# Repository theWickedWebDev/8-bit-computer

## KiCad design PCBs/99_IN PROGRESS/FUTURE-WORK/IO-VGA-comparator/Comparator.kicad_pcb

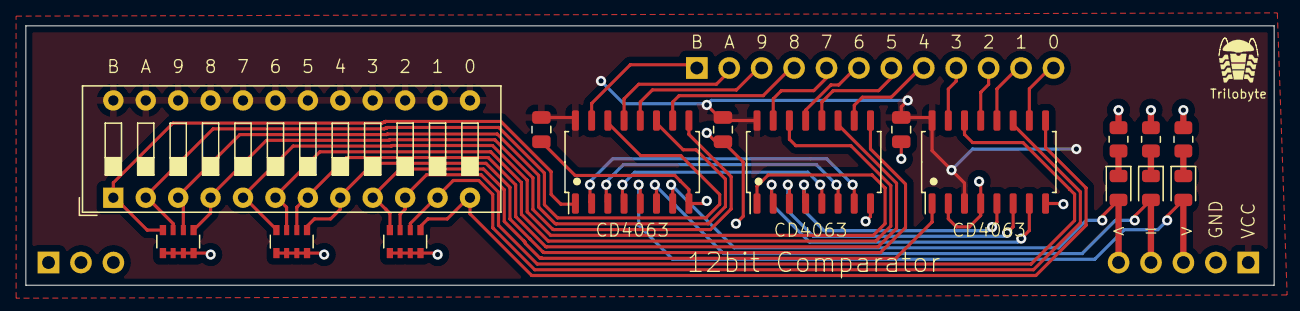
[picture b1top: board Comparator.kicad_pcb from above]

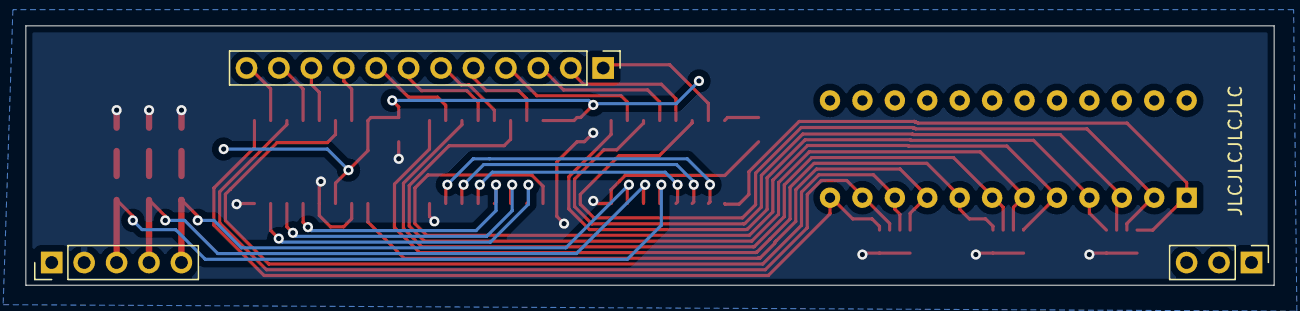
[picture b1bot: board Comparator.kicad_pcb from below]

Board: 2 copper layers, 97.8 x 20.3 mm, 19 parts (3 on the bottom side), 38 nets.

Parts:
C11, C12, C13: C; C_0805_2012Metric
D4, D5, D6: LED; LED_0805_2012Metric
J7: Conn_01x12; PinHeader_1x12_P2.54mm_Vertical
J8: Conn_01x05; PinHeader_1x05_P2.54mm_Vertical
J29: Conn_01x03; PinHeader_1x03_P2.54mm_Vertical
R4, R5, R6: R_US; R_0805_2012Metric
RN4, RN5, RN6: R_Pack04; R_Array_Convex_4x0603
SW2: SW_DIP_x12; SW_DIP_SPSTx12_Slide_9.78x32.66mm_W7.62mm_P2.54mm
U4, U5, U6: CD4063; SOIC-16_4.55x10.3mm_P1.27mm

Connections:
/Horizontal Timing/Comparator/D0_0: RN4.1 (R1.1), SW2.12, U4.9 (B0)
/Horizontal Timing/Comparator/D0_1: RN4.2 (R2.1), SW2.11, U4.11 (B1)
/Horizontal Timing/Comparator/D0_2: RN4.3 (R3.1), SW2.10, U4.14 (B2)
/Horizontal Timing/Comparator/D0_3: RN4.4 (R4.1), SW2.9, U4.1 (B3)
/Horizontal Timing/Comparator/D0_4: RN5.1 (R1.1), SW2.8, U5.9 (B0)
/Horizontal Timing/Comparator/D0_5: RN5.2 (R2.1), SW2.7, U5.11 (B1)
/Horizontal Timing/Comparator/D0_6: RN5.3 (R3.1), SW2.6, U5.14 (B2)
/Horizontal Timing/Comparator/D0_7: RN5.4 (R4.1), SW2.5, U5.1 (B3)
/Horizontal Timing/Comparator/D0_8: RN6.1 (R1.1), SW2.4, U6.9 (B0)
/Horizontal Timing/Comparator/D0_9: RN6.2 (R2.1), SW2.3, U6.11 (B1)
/Horizontal Timing/Comparator/D0_10: RN6.3 (R3.1), SW2.2, U6.14 (B2)
/Horizontal Timing/Comparator/D0_11: RN6.4 (R4.1), SW2.1, U6.1 (B3)
COUNT0: J7.12, U4.10 (A0)
COUNT1: J7.11, U4.12 (A1)
COUNT2: J7.10, U4.13 (A2)
COUNT3: J7.9, U4.15 (A3)
COUNT4: J7.8, U5.10 (A0)
COUNT5: J7.7, U5.12 (A1)
COUNT6: J7.6, U5.13 (A2)
COUNT7: J7.5, U5.15 (A3)
COUNT8: J7.4, U6.10 (A0)
COUNT9: J7.3, U6.12 (A1)
COUNT10: J7.2, U6.13 (A2)
COUNT11: J7.1, U6.15 (A3)
GND: C11.2, C12.2, C13.2, J8.2, R4.2, R5.2, R6.2, RN4.5 (R4.2), RN4.6 (R3.2), RN4.7 (R2.2), RN4.8 (R1.2), RN5.5 (R4.2), RN5.6 (R3.2), RN5.7 (R2.2), RN5.8 (R1.2), RN6.5 (R4.2), RN6.6 (R3.2), RN6.7 (R2.2), RN6.8 (R1.2), U4.2 (Ia<b), U4.4 (Ia>b), U4.8 (GND), U5.8 (GND), U6.8 (GND)
unnamed: D4.1 (K), R4.1
unnamed: D5.1 (K), R5.1
unnamed: D6.1 (K), R6.1
unnamed: U4.5 (Oa>b), U5.4 (Ia>b)
unnamed: U4.6 (Oa=b), U5.3 (Ia=b)
unnamed: U4.7 (Oa<b), U5.2 (Ia<b)
unnamed: U5.5 (Oa>b), U6.4 (Ia>b)
unnamed: U5.6 (Oa=b), U6.3 (Ia=b)
unnamed: U5.7 (Oa<b), U6.2 (Ia<b)
VCC: C11.1, C12.1, C13.1, J8.1, SW2.13, SW2.14, SW2.15, SW2.16, SW2.17, SW2.18, SW2.19, SW2.20, SW2.21, SW2.22, SW2.23, SW2.24, U4.3 (Ia=b), U4.16 (VCC), U5.16 (VCC), U6.16 (VCC)
~EQ0: D5.2 (A), J8.4, U6.6 (Oa=b)
~GT0: D6.2 (A), J8.3, U6.5 (Oa>b)
~LT0: D4.2 (A), J8.5, U6.7 (Oa<b)

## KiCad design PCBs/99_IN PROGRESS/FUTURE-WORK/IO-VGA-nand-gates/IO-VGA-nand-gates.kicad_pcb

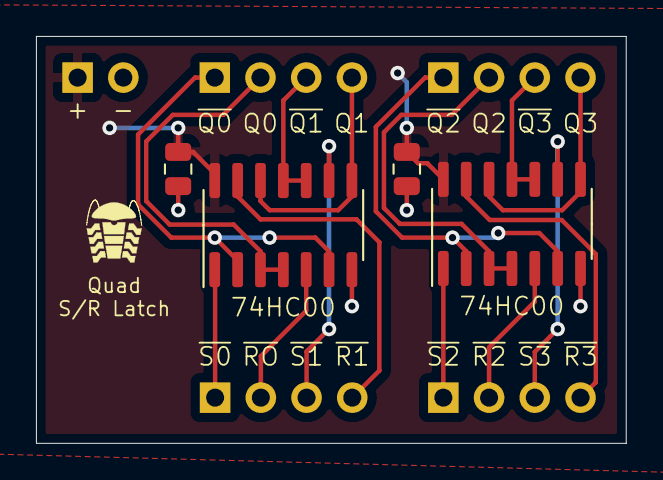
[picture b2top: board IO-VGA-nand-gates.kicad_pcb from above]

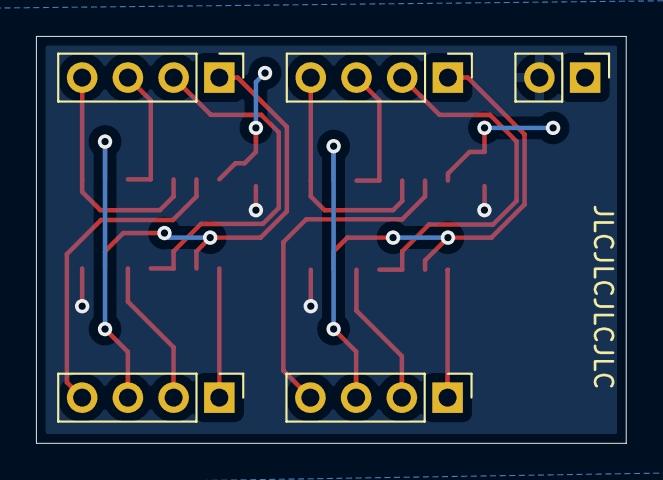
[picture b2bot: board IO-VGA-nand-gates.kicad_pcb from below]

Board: 2 copper layers, 32.8 x 22.6 mm, 9 parts (5 on the bottom side), 18 nets.

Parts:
C1, C2: C; C_0805_2012Metric
J1, J3, J4, J5: Conn_01x04; PinHeader_1x04_P2.54mm_Vertical
J2: Conn_01x02; PinHeader_1x02_P2.54mm_Vertical
U1, U2: 74LS00; SOIC-14_3.9x8.7mm_P1.27mm

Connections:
/Q0: J5.2, U1.3, U1.4
/Q1: J5.4, U1.8, U1.12
/Q2: J4.2, U2.3, U2.4
/Q3: J4.4, U2.8, U2.12
/~Q0: J5.1, U1.2, U1.6
/~Q1: J5.3, U1.10, U1.11
/~Q2: J4.1, U2.2, U2.6
/~Q3: J4.3, U2.10, U2.11
/~R0: J1.2, U1.5
/~R1: J1.4, U1.13
/~R2: J3.2, U2.5
/~R3: J3.4, U2.13
/~S0: J1.1, U1.1
/~S1: J1.3, U1.9
/~S2: J3.1, U2.1
/~S3: J3.3, U2.9
GND: C1.2, C2.2, J2.2, U1.7 (GND), U2.7 (GND)
VCC: C1.1, C2.1, J2.1, U1.14 (VCC), U2.14 (VCC)

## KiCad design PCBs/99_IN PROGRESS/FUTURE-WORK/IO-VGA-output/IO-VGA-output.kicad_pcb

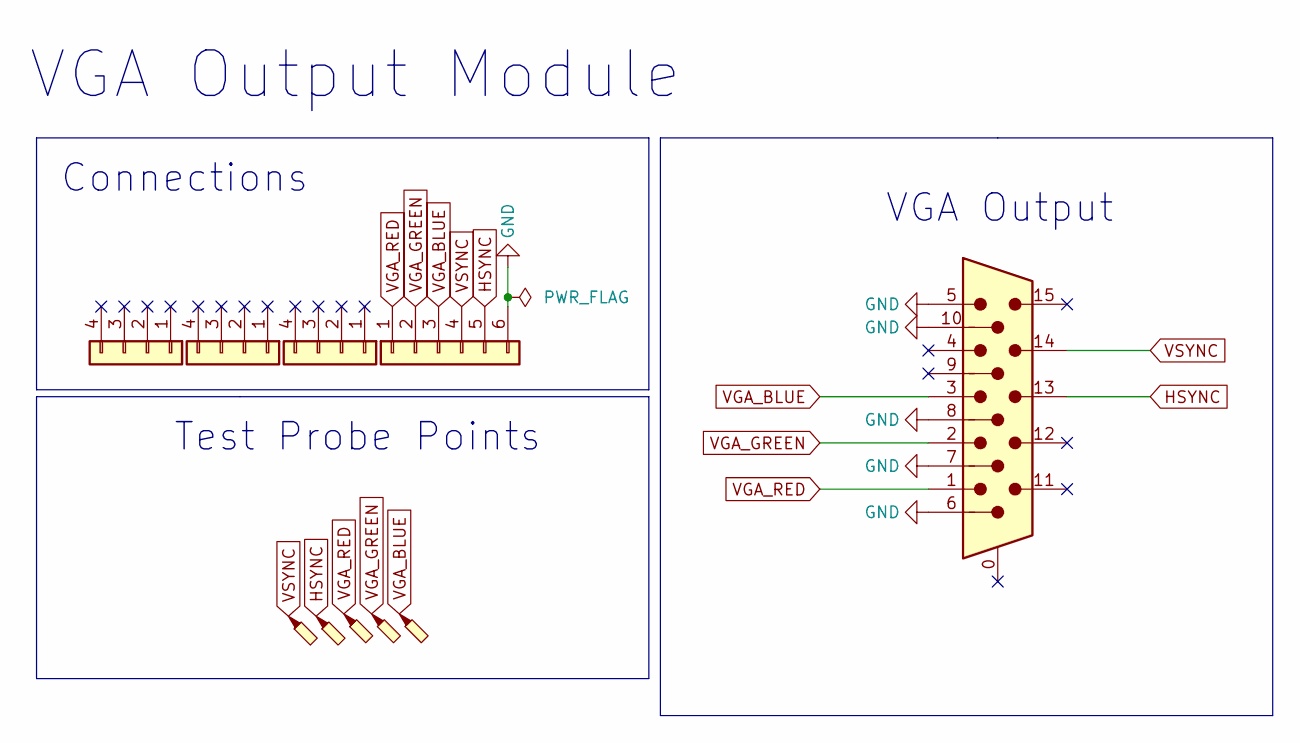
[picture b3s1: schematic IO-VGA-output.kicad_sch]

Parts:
J1: DB15_Male_HighDensity_MountingHoles; DSUB-15-HD_Female_Horizontal_P2.29x1.98mm_EdgePinOffset8.35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
J2, J4, J5: Conn_01x04; PinHeader_1x04_P2.54mm_Vertical
J3: Conn_01x06; PinHeader_1x06_P2.54mm_Vertical
TP1, TP2, TP3, TP4, TP5: TestPoint_Probe; TestPoint_Pad_D3.0mm

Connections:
GND: J1.5, J1.6, J1.7, J1.8, J1.10, J3.6
HSYNC: J1.13, J3.5, TP4.1
VGA_BLUE: J1.3, J3.3, TP1.1
VGA_GREEN: J1.2, J3.2, TP2.1
VGA_RED: J1.1, J3.1, TP3.1
VSYNC: J1.14, J3.4, TP5.1

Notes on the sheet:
VGA Output
Test Probe Points
Connections
VGA Output Module

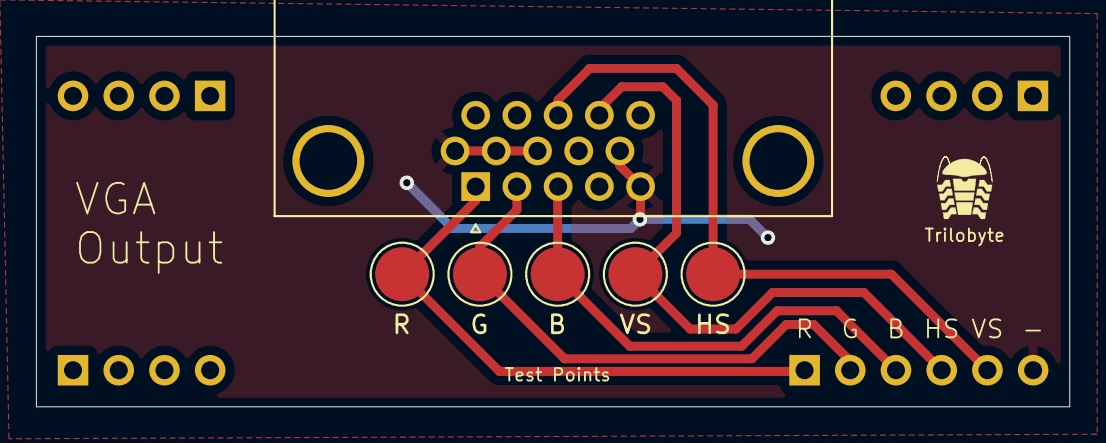
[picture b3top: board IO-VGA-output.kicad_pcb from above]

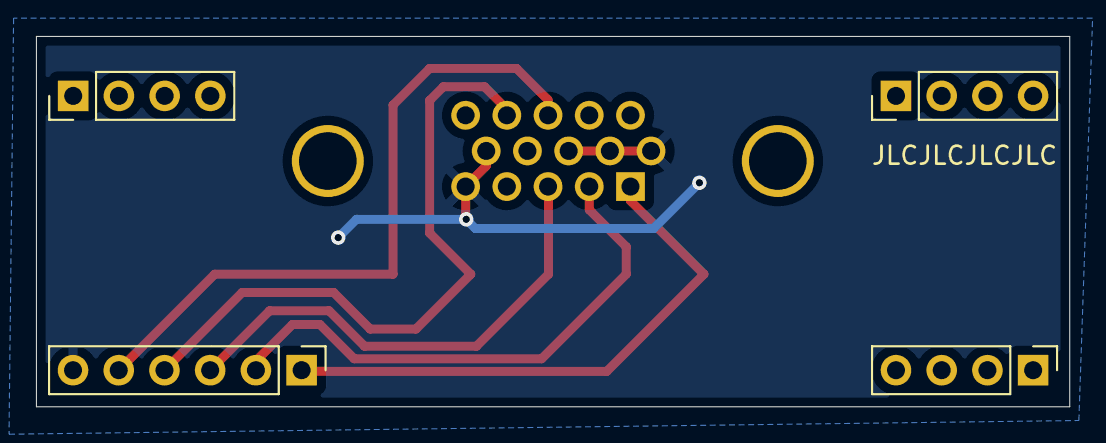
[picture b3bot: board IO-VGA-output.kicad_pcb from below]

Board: 2 copper layers, 57.4 x 20.6 mm, 10 parts (4 on the bottom side), 6 nets.

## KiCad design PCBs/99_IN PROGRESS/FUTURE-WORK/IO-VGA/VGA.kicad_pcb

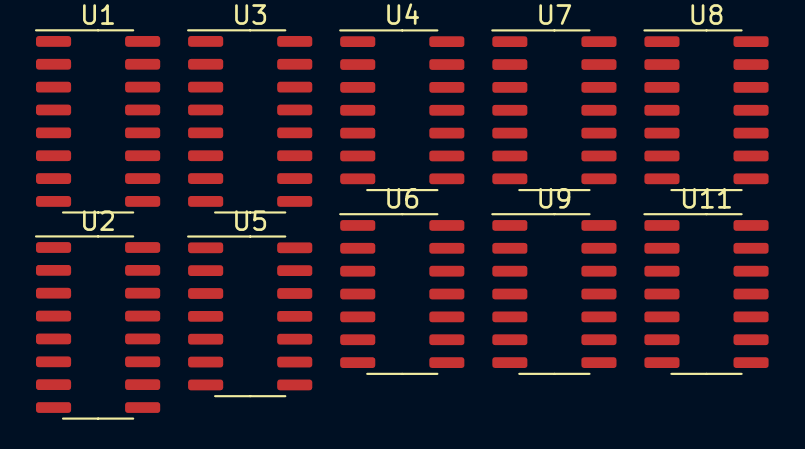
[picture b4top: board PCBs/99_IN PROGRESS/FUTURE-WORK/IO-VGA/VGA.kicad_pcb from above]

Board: 2 copper layers, 10 parts (0 on the bottom side), 2 nets, no tracks yet.

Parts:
U1, U2, U3: SN74HC161DR; SOIC-16_3.9x9.9mm_P1.27mm
U4, U5: 74HC04; SOIC-14_3.9x8.7mm_P1.27mm
U6, U7, U9, U11: CD74HC30M96; SOIC-14_3.9x8.7mm_P1.27mm
U8: SN74HC00DR; SOIC-14_3.9x8.7mm_P1.27mm

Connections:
GND: U1.8, U2.8, U3.8, U4.7, U5.7, U6.7, U7.7, U8.7, U9.7, U11.7
VCC: U1.9, U1.16, U2.9, U2.16, U3.9, U3.16, U4.14, U5.14, U6.14, U7.14, U8.14, U9.14, U11.14

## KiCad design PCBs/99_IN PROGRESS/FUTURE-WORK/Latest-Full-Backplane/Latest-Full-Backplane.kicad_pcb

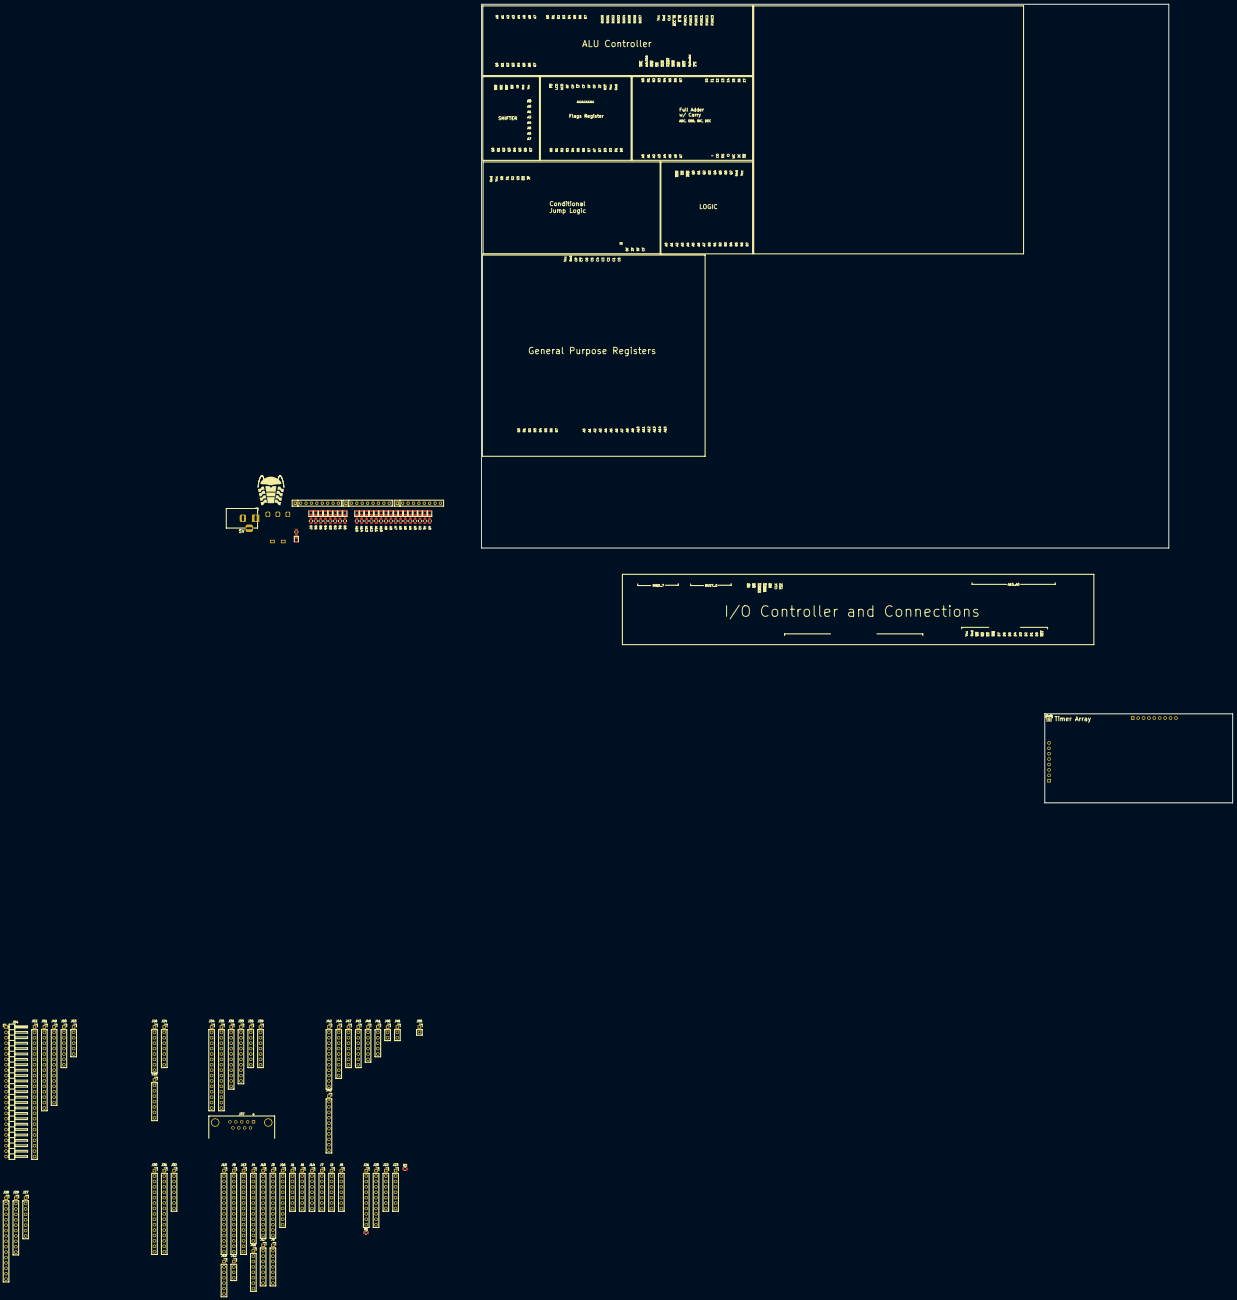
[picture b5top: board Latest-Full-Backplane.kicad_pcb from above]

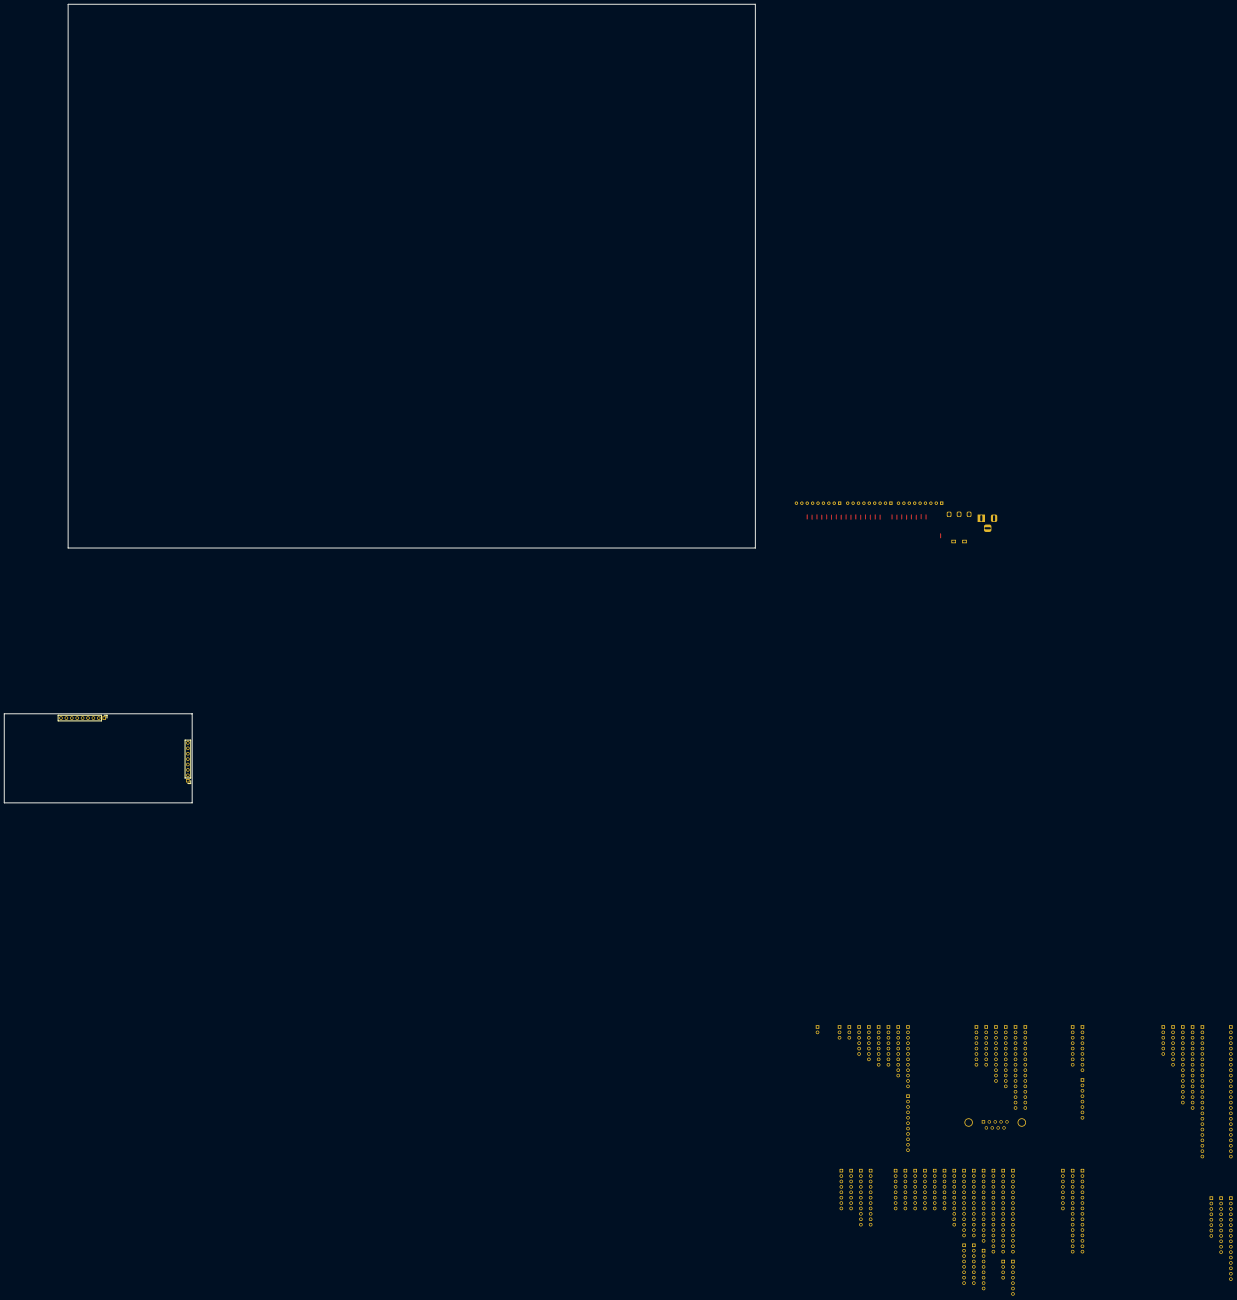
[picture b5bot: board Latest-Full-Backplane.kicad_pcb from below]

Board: 2 copper layers, 113 parts (2 on the bottom side), 160 nets.

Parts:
D1, D2, D3, D4, D5, D6, D7, D8, D9, D10, D11, D12, D13, D14, D15, D16, D17, D18, D19, D20, D21, D22, D23, D24, D25: LED; LED_0805_2012Metric
J1, J2, J5, J6, J7, J8, J11, J14, J17, J22, J23, J24, J25, J27, J32, J36, J39, J43, J47, J50: Conn_01x08; PinSocket_1x08_P2.54mm_Vertical
J1#2: Conn_01x08; PinHeader_1x08_P2.54mm_Vertical
J2#2: Conn_01x09; PinHeader_1x09_P2.54mm_Vertical
J3, J10: Conn_01x13; PinSocket_1x13_P2.54mm_Vertical
J4: Conn_01x14; PinSocket_1x14_P2.54mm_Vertical
J9, J13, J15, J28, J30, J31, J34, J35, J51: Conn_01x16; PinSocket_1x16_P2.54mm_Vertical
J12: Conn_01x04; PinSocket_1x04_P2.54mm_Vertical
J16, J21, J29, J33, J40: Conn_01x11; PinSocket_1x11_P2.54mm_Vertical
J18: Barrel_Jack_MountingPin; BarrelJack_Horizontal
J19, J48: Conn_01x07; PinSocket_1x07_P2.54mm_Vertical
J20: Conn_01x12; PinSocket_1x11_P2.54mm_Vertical
J26: Conn_01x09; PinSocket_1x09_P2.54mm_Vertical
J37: Conn_01x09; DSUB-9_Female_Horizontal_P2.77x2.84mm_EdgePinOffset4.94mm_H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
J38, J42: Conn_01x12; PinSocket_1x12_P2.54mm_Vertical
J41, J53: Conn_01x06; PinSocket_1x06_P2.54mm_Vertical
J44: Conn_01x10; PinSocket_1x10_P2.54mm_Vertical
J45, J46: Conn_01x03; PinSocket_1x03_P2.54mm_Vertical
J49: Conn_01x15; PinSocket_1x15_P2.54mm_Vertical
J52: Conn_01x25; PinSocket_1x25_P2.54mm_Vertical
J54: Conn_01x25; PinHeader_1x25_P2.54mm_Horizontal
J55: Conn_01x02; PinSocket_1x02_P2.54mm_Vertical
R1, R2, R3, R4, R5, R6, R7, R8, R9, R10, R11, R12, R13, R14, R15, R16, R17, R18, R19, R20, R21, R22, R23, R24, R25, R26, R27: R_US; R_0805_2012Metric
RN2, RN3: R_Network08; R_Array_SIP9
RN': R_Network08; R_Array_SIP9
SW1: SW_DPDT_x2; 100SP1T1B4M6RE

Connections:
/ADDR0: J20.1, J23.1, J29.1, J43.1
/ADDR1: J20.2, J23.2, J29.2, J43.2
/ADDR2: J20.3, J23.3, J29.3, J43.3
/ADDR3: J20.4, J23.4, J29.4, J43.4
/ADDR4: J20.5, J23.5, J29.5, J30.4, J43.5
/ADDR5: J20.6, J23.6, J29.6, J43.6
/ADDR6: J20.7, J23.7, J29.7, J43.7
/ADDR7: J20.8, J23.8, J26.9, J29.8, J43.8
/ADDR8: J20.9, J26.8, J29.9
/ADDR9: J20.10, J26.7, J29.10
/ADDR10: J20.11, J26.6, J29.11
/ALU/ALU_A0: J17.1, J18.1, J19.1
/ALU/ALU_A1: J17.2, J18.2, J19.2
/ALU/ALU_A2: J17.3, J18.3, J19.3
/ALU/ALU_A3: J17.4, J19.4
/ALU/ALU_A4: J17.5, J19.5
/ALU/ALU_A5: J16.11, J17.6, J19.6
/ALU/ALU_A6: J16.10, J17.7, J19.7
/ALU/ALU_A7: J6.6, J16.9, J17.8
/ALU/ALU_B0: J14.1, J15.1, J16.8
/ALU/ALU_B1: J14.2, J15.2, J16.7
/ALU/ALU_B2: J14.3, J15.3, J16.6
/ALU/ALU_B3: J14.4, J15.4, J16.5
/ALU/ALU_B4: J14.5, J15.5, J16.4
/ALU/ALU_B5: J14.6, J15.6, J16.3
/ALU/ALU_B6: J14.7, J15.7, J16.2
/ALU/ALU_B7: J6.5, J14.8, J15.8, J16.1
/ALU/ALU_FUNC_0: J2.4, J36.6
/ALU/ALU_FUNC_1: J2.3, J36.7
/ALU/ALU_FUNC_2: J2.2, J36.8
/ALU/ALU_Q0: J10.4, J11.8, J13.8
/ALU/ALU_Q1: J10.5, J11.7, J13.7
/ALU/ALU_Q2: J10.6, J11.6, J13.6
/ALU/ALU_Q3: J10.7, J11.5, J13.5
/ALU/ALU_Q4: J10.8, J11.4, J12.4, J13.4
/ALU/ALU_Q5: J10.9, J11.3, J12.3, J13.3
/ALU/ALU_Q6: J6.8, J10.10, J11.2, J12.2, J13.2
/ALU/ALU_Q7: J6.7, J10.11, J11.1, J12.1, J13.1
/ALU/CF: J1.7, J4.4, J7.4
/ALU/CLOCK: J21.9, J24.4, J30.6, J34.2, J40.5
/ALU/JCC_ADR0: J3.6, J37.1
/ALU/JCC_ADR1: J3.5, J37.3
/ALU/JCC_ADR2: J3.4, J37.2
/ALU/JCC_ADR3: J3.3, J37.4
/ALU/OF: J1.5, J4.1
/ALU/SF: J1.6, J4.3
/ALU/ZF: J1.4, J4.2
/ALU/~JCC_EN: J3.2, J37.5
/ALU/~JCC_LD_PC_COND: J3.1, J37.6
/ALU/~LATCH_A: J2.8, J36.5
/ALU/~LATCH_B: J2.7, J36.4
/ALU/~LATCH_FLAGS: J1.8, J36.1
/BUS0: J6.1, J9.1, J25.8, J28.1, J31.8, J33.1, J45.2, J51.2
/BUS1: J6.2, J9.2, J25.7, J28.2, J31.7, J33.2, J45.3, J51.3
/BUS2: J6.3, J9.3, J25.6, J28.3, J31.6, J33.3, J41.6, J51.4
/BUS3: J6.4, J9.4, J25.5, J28.4, J31.5, J33.4, J41.5, J51.5
/BUS4: J9.5, J25.4, J28.5, J31.4, J33.5, J41.4, J51.6
/BUS5: J9.6, J25.3, J28.6, J31.3, J33.6, J41.3, J51.7
/BUS6: J9.7, J25.2, J28.7, J31.2, J33.7, J41.2, J51.8
/BUS7: J9.8, J25.1, J28.8, J31.1, J33.8, J41.1, J51.9
/Control Unit/GPR0: J27.1, J35.8
/Control Unit/GPR1: J27.2, J35.7
/Control Unit/GPR2: J27.3, J35.6
/Control Unit/GPR3: J27.4, J35.5
/Control Unit/GPR4: J27.5, J35.4
/Control Unit/GPR5: J27.6, J35.3
/Control Unit/GPR6: J27.7, J35.2
/Control Unit/~CLOCK: J34.1, J40.6
/Control Unit/~CPU_INTERRUPT: J30.1, J34.4
/Control Unit/~IO_REQUEST: J34.5, J40.3
/Control Unit/~IRQ_MASK_PORT_EN: J30.5, J34.6
/Control Unit/~LATCH_CODE_SEGMENT: J24.7, J38.3
/Control Unit/~LATCH_DATA_SEGMENT: J24.6, J38.2
/Control Unit/~LATCH_MAR: J24.5, J38.1
/Control Unit/~LATCH_STACK_SEGMENT: J24.8, J38.4
/Control Unit/~PC_BUS_OUT: J21.4, J39.1
/Control Unit/~PC_DEC: J22.7, J39.4
/Control Unit/~PC_INC: J22.6, J39.3
/Control Unit/~PC_LOAD: J21.5, J39.2
/Control Unit/~READ: J30.3, J34.8, J40.1, J44.3, J51.12
/Control Unit/~RESET: J34.3, J35.1
/Control Unit/~SP_BUS_OUT: J22.4, J39.5
/Control Unit/~SP_DEC: J21.7, J39.8
/Control Unit/~SP_INC: J21.6, J39.7
/Control Unit/~SP_LOAD: J22.5, J39.6
/Control Unit/~WRITE: J30.2, J34.7, J40.2, J44.4, J51.13
/GPR/~GPR7: J21.8, J22.8, J24.3, J27.8, J40.4, J45.1, J51.1
/Stack Pointer/~PC_ADDR_OUT: J21.3, R1.2
/Stack Pointer/~SP_ADDR_OUT: J22.3, R2.2
ADC_SBB: J5.2, J7.3
ADDER_OUT: J5.6, J7.1
ADDR0: D16.2 (A), RN2.9 (R8)
ADDR1: D15.2 (A), RN2.8 (R7)
ADDR2: D14.2 (A), RN2.7 (R6)
ADDR3: D13.2 (A), RN2.6 (R5)
ADDR4: D12.2 (A), RN2.5 (R4)
ADDR5: D11.2 (A), RN2.4 (R3)
ADDR6: D10.2 (A), RN2.3 (R2)
ADDR7: D9.2 (A), RN2.2 (R1)
ADDR8: D8.2 (A), RN'.9 (R8)
ADDR9: D7.2 (A), RN'.8 (R7)
ADDR10: D6.2 (A), RN'.7 (R6)
ADDR11: D5.2 (A), RN'.6 (R5)
ADDR12: D4.2 (A), RN'.5 (R4)
ADDR13: D3.2 (A), RN'.4 (R3)
ADDR14: D2.2 (A), RN'.3 (R2)
ADDR15: D1.2 (A), RN'.2 (R1)
BUS0: D25.2 (A), J1#2.1, RN3.9 (R8)
BUS1: D24.2 (A), J1#2.2, RN3.8 (R7)
BUS2: D22.2 (A), J1#2.3, RN3.7 (R6)
BUS3: D21.2 (A), J1#2.4, RN3.6 (R5)
BUS4: D20.2 (A), J1#2.5, RN3.5 (R4)
BUS5: D19.2 (A), J1#2.6, RN3.4 (R3)
BUS6: D18.2 (A), J1#2.7, RN3.3 (R2)
BUS7: D17.2 (A), J1#2.8, RN3.2 (R1)
GND: J1.1, J1.3, J2#2.2, J3.8, J7.7, J8.6, J10.12, J21.10, J24.2, J30.7, J33.9, J44.2, J51.14, J52.5, J53.6, J54.6, J55.2, R1.1, R2.1, R3.2, R4.2, R5.2, R6.2, R7.2, R8.2, R9.2, R10.2, R11.2, R12.2, R13.2, R14.2, R15.2, R16.2, R17.2, R18.2, R19.2, R20.2, R21.2, R22.2, R23.2, R24.2, R25.2, R26.2, R27.2, RN2.1 (common), RN3.1 (common), RN'.1 (common)
unnamed: D1.1 (K), R3.1
unnamed: D2.1 (K), R4.1
unnamed: D3.1 (K), R5.1
unnamed: D4.1 (K), R6.1
unnamed: D5.1 (K), R7.1
unnamed: D6.1 (K), R8.1
unnamed: D7.1 (K), R9.1
unnamed: D8.1 (K), R10.1
unnamed: D9.1 (K), R11.1
unnamed: D10.1 (K), R12.1
unnamed: D11.1 (K), R13.1
unnamed: D12.1 (K), R14.1
unnamed: D13.1 (K), R15.1
unnamed: D14.1 (K), R16.1
unnamed: D15.1 (K), R17.1
unnamed: D16.1 (K), R18.1
unnamed: D17.1 (K), R19.1
unnamed: D18.1 (K), R20.1
unnamed: D19.1 (K), R21.1
unnamed: D20.1 (K), R22.1
unnamed: D21.1 (K), R23.1
unnamed: D22.1 (K), R24.1
unnamed: D23.1 (K), R25.1
unnamed: D24.1 (K), R26.1
unnamed: D25.1 (K), R27.1
unnamed: J55.1, SW1.5 (B)
SER_CTS: J52.8, J53.5, J54.5
SER_RTS: J52.7, J53.1, J54.1
SER_RX: J52.2, J53.2, J54.2
SER_TX: J52.3, J53.3, J54.3
VCC: D23.2 (A), J1.2, J2#2.1, J3.7, J7.8, J8.7, J10.13, J21.11, J24.1, J30.8, J33.10, J44.1, J51.15, SW1.4 (A)
~AND: J5.3, J10.3
~IRQ1: J32.7, J42.2, J48.7
~IRQ2: J32.6, J42.3, J48.6
~IRQ3: J32.5, J42.4, J48.5
~IRQ4: J32.4, J42.5, J48.4
~IRQ5: J32.3, J42.6, J48.3
~IRQ6: J32.2, J42.7, J48.2
~IRQ7: J32.1, J42.8, J48.1
~OR: J5.4, J10.2
~SHIFTER_ARI: J5.8, J8.4
~SHIFTER_SHL: J5.1, J8.2
~SHIFTER_SHR: J5.7, J8.1
~XOR: J5.5, J10.1

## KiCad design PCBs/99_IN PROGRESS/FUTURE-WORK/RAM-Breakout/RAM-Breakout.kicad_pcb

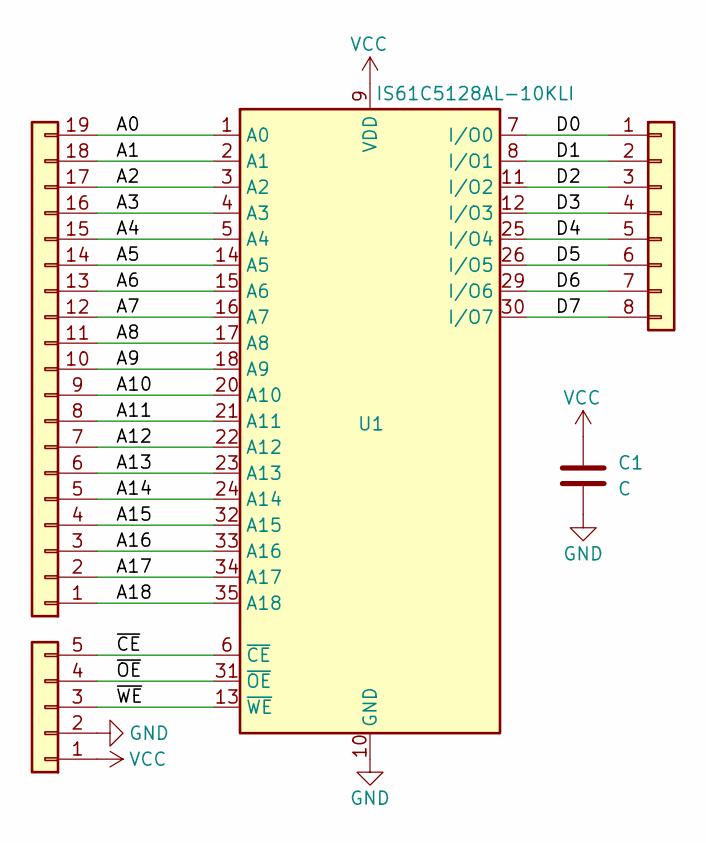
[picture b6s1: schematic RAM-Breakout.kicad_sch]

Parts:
C1: C; C_0805_2012Metric
J1: Conn_01x19; PinHeader_1x19_P2.54mm_Vertical
J2: Conn_01x05; PinHeader_1x05_P2.54mm_Vertical
J3: Conn_01x08; PinHeader_1x08_P2.54mm_Vertical
U1: IS61C5128AL-10KLI; SOJ-36_10.16x23.49mm_P1.27mm

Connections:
/A0: J1.19, U1.1 (A0)
/A1: J1.18, U1.2 (A1)
/A2: J1.17, U1.3 (A2)
/A3: J1.16, U1.4 (A3)
/A4: J1.15, U1.5 (A4)
/A5: J1.14, U1.14 (A5)
/A6: J1.13, U1.15 (A6)
/A7: J1.12, U1.16 (A7)
/A8: J1.11, U1.17 (A8)
/A9: J1.10, U1.18 (A9)
/A10: J1.9, U1.20 (A10)
/A11: J1.8, U1.21 (A11)
/A12: J1.7, U1.22 (A12)
/A13: J1.6, U1.23 (A13)
/A14: J1.5, U1.24 (A14)
/A15: J1.4, U1.32 (A15)
/A16: J1.3, U1.33 (A16)
/A17: J1.2, U1.34 (A17)
/A18: J1.1, U1.35 (A18)
/D0: J3.1, U1.7 (I/O0)
/D1: J3.2, U1.8 (I/O1)
/D2: J3.3, U1.11 (I/O2)
/D3: J3.4, U1.12 (I/O3)
/D4: J3.5, U1.25 (I/O4)
/D5: J3.6, U1.26 (I/O5)
/D6: J3.7, U1.29 (I/O6)
/D7: J3.8, U1.30 (I/O7)
/~CE: J2.5, U1.6 (~CE)
/~OE: J2.4, U1.31 (~OE)
/~WE: J2.3, U1.13 (~WE)
GND: C1.2, J2.2, U1.10 (GND), U1.28 (GND)
VCC: C1.1, J2.1, U1.9 (VDD), U1.27 (VDD)

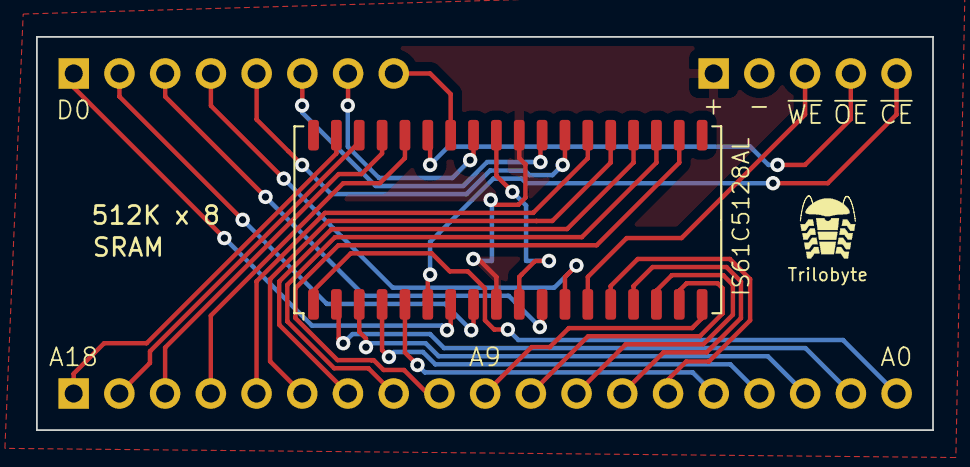
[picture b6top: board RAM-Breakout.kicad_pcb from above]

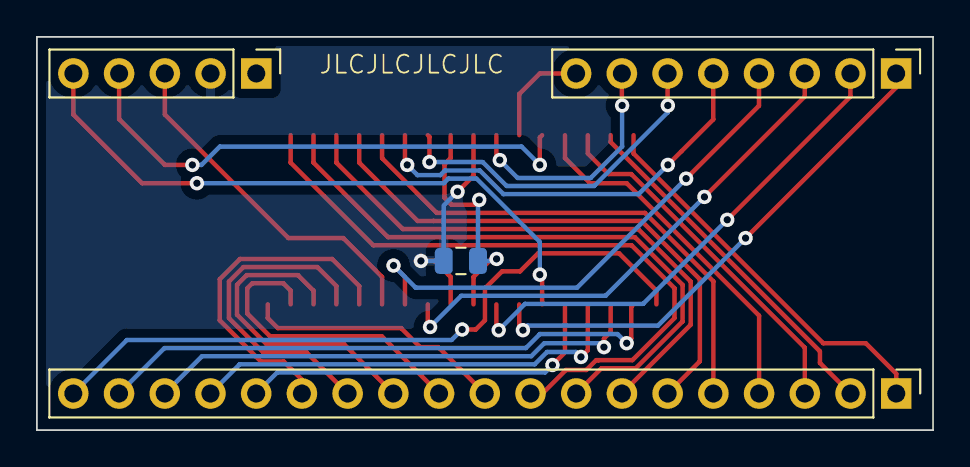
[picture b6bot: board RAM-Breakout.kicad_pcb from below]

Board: 2 copper layers, 49.8 x 21.8 mm, 5 parts (4 on the bottom side), 32 nets.

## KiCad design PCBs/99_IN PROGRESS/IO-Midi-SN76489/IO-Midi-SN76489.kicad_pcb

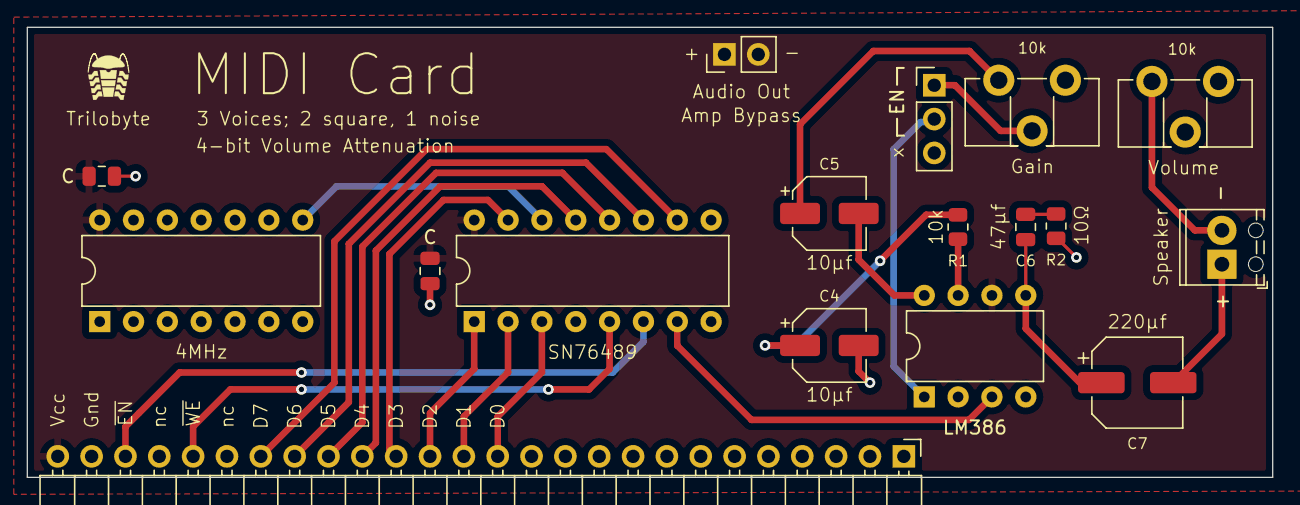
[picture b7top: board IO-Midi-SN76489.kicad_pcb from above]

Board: 2 copper layers, 93.5 x 33.8 mm, 17 parts (0 on the bottom side), 24 nets.

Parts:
C1, C3: C; C_0805_2012Metric
C4, C5: 10µf; CP_Elec_5x5.4
C6: 47µf; C_0805_2012Metric
C7: 220µf; CP_Elec_6.3x7.7
J1: Conn_01x26; PinHeader_1x26_P2.54mm_Horizontal
J2: Conn_01x03; PinHeader_1x03_P2.54mm_Vertical
J3: Screw_Terminal_01x02; TerminalBlock_Phoenix_MPT-0,5-2-2.54_1x02_P2.54mm_Horizontal
J4: Conn_01x02; PinHeader_1x02_P2.54mm_Vertical
R1: 10k; R_0805_2012Metric
R2: 10Ω; R_0805_2012Metric
RV1, RV2: 10k; Potentiometer_ACP_CA9-H3,8_Horizontal
U2: SN76489; DIP-16_W7.62mm
U3: LM386; DIP-8_W7.62mm
Y1: 4MHz; Crystal_DIP_4_14

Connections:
4MHZ: U2.14 (CLOCK), Y1.3
AUDIO_OUT: J4.1, U2.7 (OUT), U3.3 (+)
BUS0: J1.13, U2.3 (D0)
BUS1: J1.14, U2.2 (D1)
BUS2: J1.15, U2.1 (D2)
BUS3: J1.16, U2.15 (D3)
BUS4: J1.17, U2.13 (D4)
BUS5: J1.18, U2.12 (D5)
BUS6: J1.19, U2.11 (D6)
BUS7: J1.20, U2.10 (D7)
GND: C1.2, C3.2, C4.2, J1.25, J4.2, R2.2, RV2.2, U2.8 (GND), U3.2 (-), U3.4 (GND), Y1.2
unnamed: C4.1, R1.1
unnamed: C5.1, RV1.3
unnamed: C5.2, U3.8 (GAIN)
unnamed: C6.1, C7.1, U3.5
unnamed: C6.2, R2.1
unnamed: J2.1, RV1.2
unnamed: R1.2, U3.7 (BYPASS)
unnamed: J2.2, U3.1 (GAIN)
SPEAKER+: C7.2, J3.1
SPEAKER-: J3.2, RV2.3
VCC: C1.1, C3.1, J1.26, U2.16 (VCC), U3.6 (V+), Y1.4
~EN: J1.24, U2.6 (~CE)
~WRITE: J1.22, U2.5 (~WE)

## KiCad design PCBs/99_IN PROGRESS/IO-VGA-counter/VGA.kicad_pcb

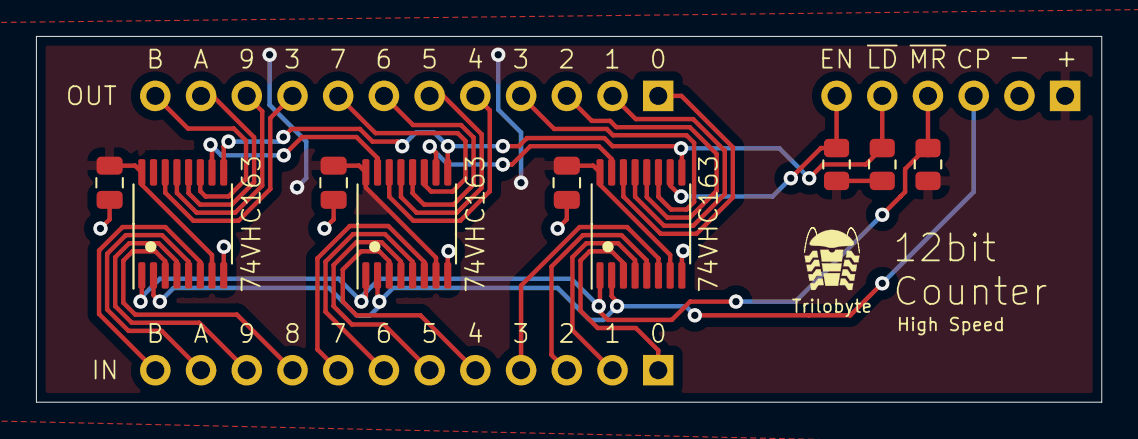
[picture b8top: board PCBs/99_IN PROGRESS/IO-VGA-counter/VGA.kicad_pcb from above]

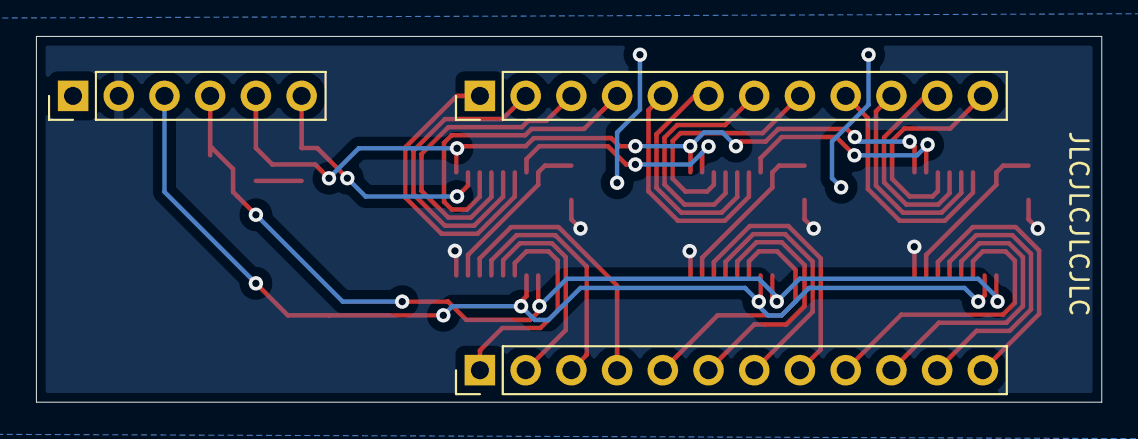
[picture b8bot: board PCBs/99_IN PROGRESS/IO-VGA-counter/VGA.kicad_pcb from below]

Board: 2 copper layers, 59.2 x 20.3 mm, 12 parts (3 on the bottom side), 32 nets.

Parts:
C1, C2, C3: C; C_0805_2012Metric
J1, J2: Conn_01x12; PinHeader_1x12_P2.54mm_Vertical
J3: Conn_01x06; PinHeader_1x06_P2.54mm_Vertical
R1, R2, R3: R_US; R_0805_2012Metric
U1, U2, U3: 74LS163; TSSOP-16_4.4x5mm_P0.65mm

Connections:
/CLOCK: J3.3, U1.2 (CP), U2.2 (CP), U3.2 (CP)
/D0: J1.1, U1.3 (D0)
/D1: J1.2, U1.4 (D1)
/D2: J1.3, U1.5 (D2)
/D3: J1.4, U1.6 (D3)
/D4: J1.5, U2.3 (D0)
/D5: J1.6, U2.4 (D1)
/D6: J1.7, U2.5 (D2)
/D7: J1.8, U2.6 (D3)
/D8: J1.9, U3.3 (D0)
/D9: J1.10, U3.4 (D1)
/D10: J1.11, U3.5 (D2)
/D11: J1.12, U3.6 (D3)
/EN: J3.6, R1.1, U1.10 (CET)
/Q0: J2.1, U1.14 (Q0)
/Q1: J2.2, U1.13 (Q1)
/Q2: J2.3, U1.12 (Q2)
/Q3: J2.4, U1.11 (Q3)
/Q4: J2.5, U2.14 (Q0)
/Q5: J2.6, U2.13 (Q1)
/Q6: J2.7, U2.12 (Q2)
/Q7: J2.8, U2.11 (Q3)
/Q8: J2.9, U3.14 (Q0)
/Q9: J2.10, U3.13 (Q1)
/Q10: J2.11, U3.12 (Q2)
/Q11: J2.12, U3.11 (Q3)
/~LOAD: J3.5, R2.1, U1.9 (~PE), U2.9 (~PE), U3.9 (~PE)
/~RESET: J3.4, R3.1, U1.1 (~MR), U2.1 (~MR), U3.1 (~MR)
GND: C1.2, C2.2, C3.2, J3.2, U1.8 (GND), U2.8 (GND), U3.8 (GND)
unnamed: U1.15 (TC), U2.10 (CET)
unnamed: U2.15 (TC), U3.10 (CET)
VCC: C1.1, C2.1, C3.1, J3.1, R1.2, R2.2, R3.2, U1.7 (CEP), U1.16 (VCC), U2.7 (CEP), U2.16 (VCC), U3.7 (CEP), U3.16 (VCC)
